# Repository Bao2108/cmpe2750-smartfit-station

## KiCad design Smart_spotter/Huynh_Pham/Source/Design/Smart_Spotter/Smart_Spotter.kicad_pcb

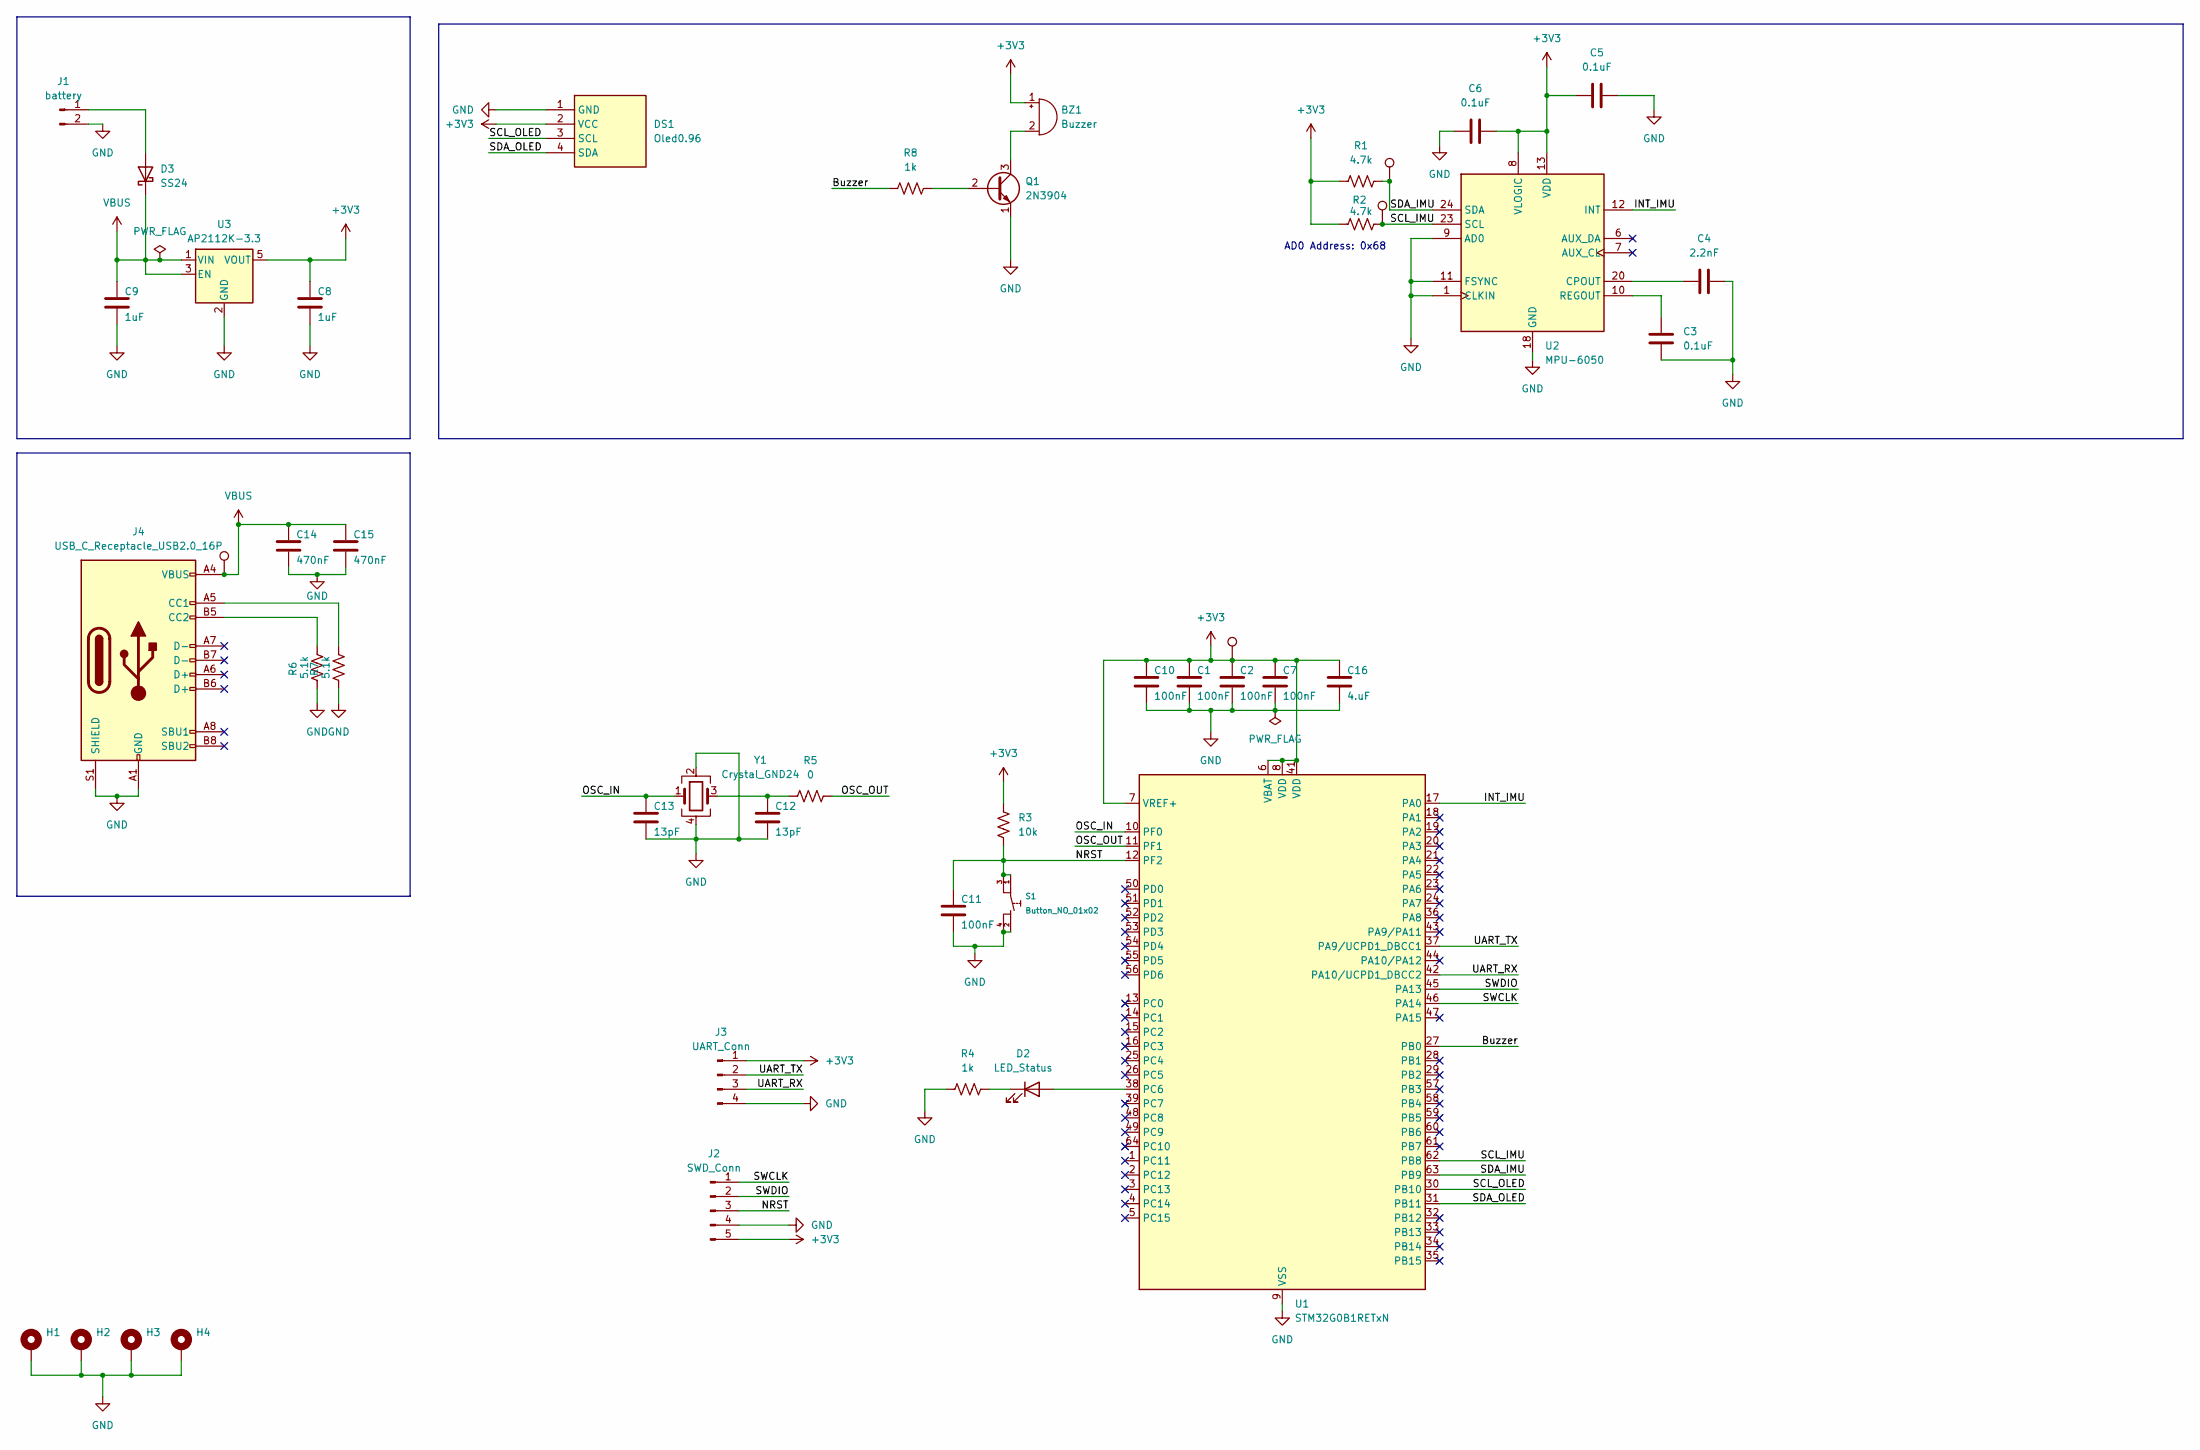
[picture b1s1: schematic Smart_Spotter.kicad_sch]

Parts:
BZ1: Buzzer; Buzzer_12x9.5RM7.6
C1, C2, C7, C10, C11: 100nF; C_0603_1608Metric
C3, C5, C6: 0.1uF; C_0603_1608Metric
C4: 2.2nF; C_0603_1608Metric
C8, C9: 1uF; C_0603_1608Metric
C12, C13: 13pF; C_0603_1608Metric
C14, C15: 470nF; C_0603_1608Metric
C16: 4.uF; C_0603_1608Metric
D2: LED_Status; LED_0603_1608Metric
D3: SS24; D_SMA
DS1: Oled0.96; MODULE_DM-OLED096-636; Manufacturer_Part_Number MDOB128064V2V-YI
H1, H2, H3, H4: MountingHole_Pad; MountingHole_2.7mm_Pad_Via
J1: battery; JST_PH_B2B-PH-K_1x02_P2.00mm_Vertical
J2: SWD_Conn; PinHeader_1x05_P2.54mm_Horizontal
J3: UART_Conn; PinHeader_1x04_P2.54mm_Vertical
J4: USB_C_Receptacle_USB2.0_16P; USB_C_Receptacle_GCT_USB4105-xx-A_16P_TopMnt_Horizontal
Q1: 2N3904; TO-92_Inline
R1, R2: 4.7k; R_0603_1608Metric
R3: 10k; R_0603_1608Metric
R4, R8: 1k; R_0603_1608Metric
R5: 0; R_0603_1608Metric
R6, R7: 5.1k; R_0603_1608Metric
S1: Button_NO_01x02; SW_Push_1P1T_NO_6x6mm_H9.5mm
TP1: SCL_IMU_TP; TestPoint_Pad_D1.5mm
TP2, TP3, TP4: SDA_IMU_TP; TestPoint_Pad_D1.5mm
U1: STM32G0B1RETxN; LQFP-64_10x10mm_P0.5mm
U2: MPU-6050; InvenSense_QFN-24_4x4mm_P0.5mm
U3: AP2112K-3.3; SOT-23-5
Y1: Crystal_GND24; Crystal_SMD_0603-4Pin_6.0x3.5mm

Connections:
+3V3: BZ1.1 (+), C1.1, C2.1, C5.1, C6.2, C7.1, C8.1, C10.1, C16.1, DS1.2 (VCC), J2.5, J3.1, R1.1, R2.1, R3.2, TP3.1, U1.6 (VBAT), U1.7 (VREF+), U1.8 (VDD), U1.41 (VDD), U2.8 (VLOGIC), U2.13 (VDD), U3.5 (VOUT)
/Buzzer: R8.1, U1.27 (PB0)
/INT_IMU: U1.17 (PA0), U2.12 (INT)
/NRST: C11.1, J2.3, R3.1, S1.1, S1.3, U1.12 (PF2)
/OSC_IN: C13.1, U1.10 (PF0), Y1.1
/OSC_OUT: R5.2, U1.11 (PF1)
/SCL_IMU: R2.2, TP1.1, U1.62 (PB8), U2.23 (SCL)
/SCL_OLED: DS1.3 (SCL), U1.30 (PB10)
/SDA_IMU: R1.2, TP2.1, U1.63 (PB9), U2.24 (SDA)
/SDA_OLED: DS1.4 (SDA), U1.31 (PB11)
/SWCLK: J2.1, U1.46 (PA14)
/SWDIO: J2.2, U1.45 (PA13)
/UART_RX: J3.3, U1.42 (PA10/UCPD1_DBCC2)
/UART_TX: J3.2, U1.37 (PA9/UCPD1_DBCC1)
GND: C1.2, C2.2, C3.2, C4.2, C5.2, C6.1, C7.2, C8.2, C9.2, C10.2, C11.2, C12.2, C13.2, C14.2, C15.2, C16.2, DS1.1 (GND), H1.1, H2.1, H3.1, H4.1, J1.2, J2.4, J3.4, J4.A1 (GND), J4.A12 (GND), J4.B1 (GND), J4.B12 (GND), J4.S1 (SHIELD), Q1.1 (E), R4.1, R6.1, R7.1, S1.2, S1.4, U1.9 (VSS), U1.40 (VSS), U2.1 (CLKIN), U2.9 (AD0), U2.11 (FSYNC), U2.18 (GND), U3.2 (GND), Y1.2, Y1.4
unnamed: BZ1.2 (-), Q1.3 (C)
unnamed: C12.1, R5.1, Y1.3
unnamed: D2.2 (A), U1.38 (PC6)
unnamed: D2.1 (K), R4.2
unnamed: D3.2 (A), J1.1
unnamed: J4.A5 (CC1), R7.2
unnamed: J4.B5 (CC2), R6.2
unnamed: Q1.2 (B), R8.2
unnamed: C4.1, U2.20 (CPOUT)
unnamed: C3.1, U2.10 (REGOUT)
VBUS: C9.1, C14.1, C15.1, D3.1 (K), J4.A4 (VBUS), J4.A9 (VBUS), J4.B4 (VBUS), J4.B9 (VBUS), TP4.1, U3.1 (VIN), U3.3 (EN)

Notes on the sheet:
AD0 Address: 0x68

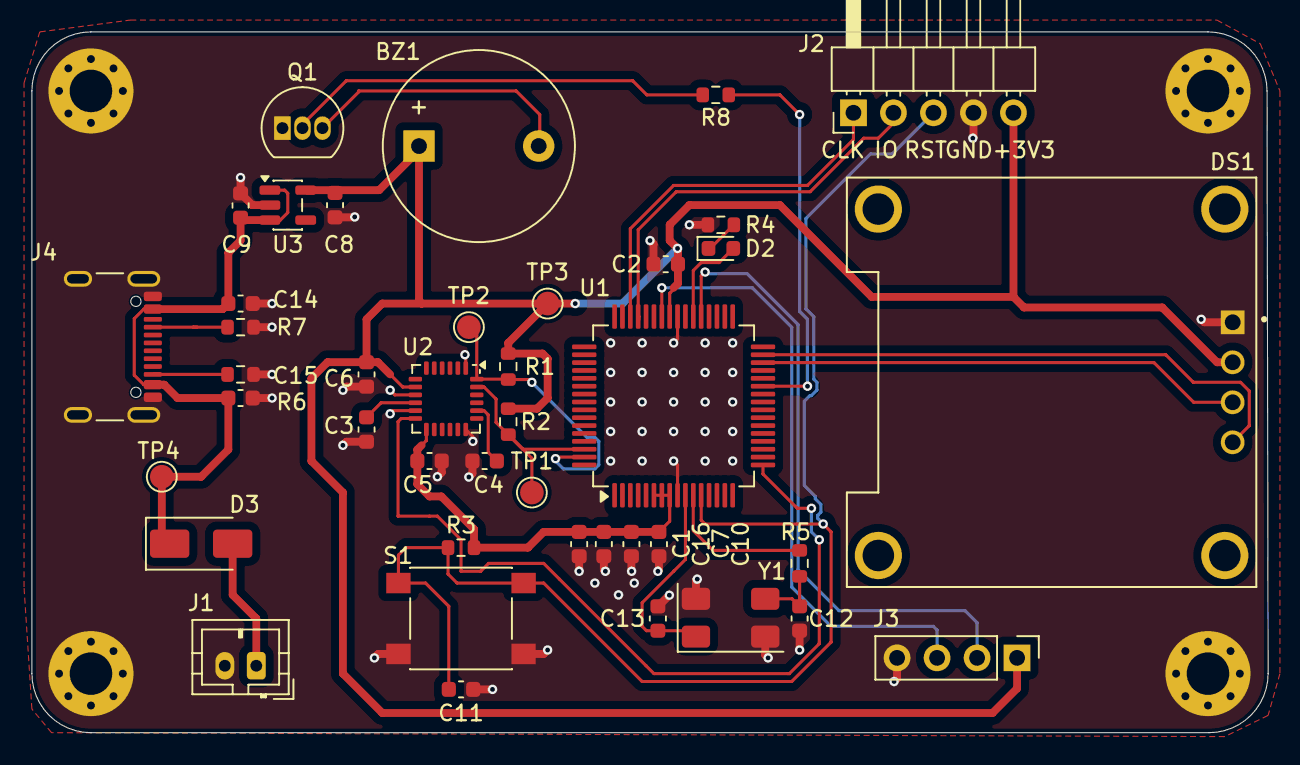
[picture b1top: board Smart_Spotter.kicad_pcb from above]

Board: 2 copper layers, 78.5 x 44.5 mm, 46 parts (0 on the bottom side), 26 nets.

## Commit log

2026-01-16 proposal uploaded
2026-03-13 pcb update
2026-04-07 proof_of_life_breadboard schematic added
2026-04-12 proof-of-life breadboard
